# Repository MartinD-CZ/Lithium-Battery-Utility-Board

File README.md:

# Lithium Battery Utility Board

*see the article [here](http://embedblog.eu/?p=91)!*

versions (see the changelog for more information):
* V1.0 - proven, initial release
* V1.1 - minor tweaks, **not proven**
* V1.2 - major tweaks, proven

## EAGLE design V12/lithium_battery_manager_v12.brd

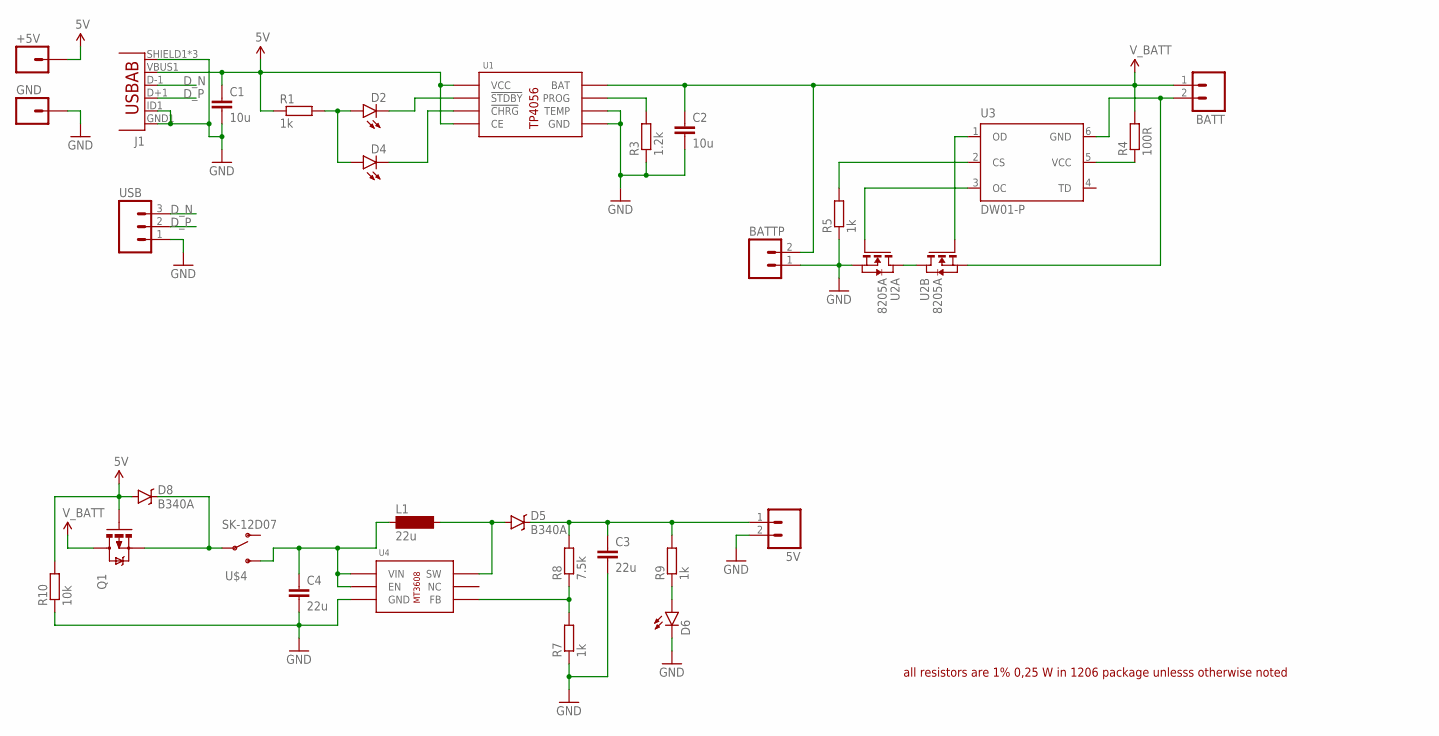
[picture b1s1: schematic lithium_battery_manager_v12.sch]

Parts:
5V: M02PTH3; 1X02_LONGPADS
+5V: M01OFFSET; 1X01_OFFSET
BATT: M02PTH3; 1X02_LONGPADS
BATTP: M02PTH3; 1X02_LONGPADS
C1, C2: 10u; C1206
C3, C4: 22u; C1206
D2, D4, D6: LED-CONN; LED5MM
D5, D8: B340A; SMA-DIODE
GND: M01OFFSET; 1X01_OFFSET
J1: USB-ABCONN-11794; USB-AB-MICRO-SMD_V03
L1: 22u; MS85
Q1: MOSFET-PCHANNEL; SOT23-3
R1, R5, R7, R9: 1k; R1206
R3: 1.2k; R1206
R4: 100R; R1206
R8: 7.5k; R1206
R10: 10k; R1206
U1: TP4056; SOP8
U2: 8205A; TSSOP8
U3: DW01-P; SOT23-6L
U4: MT3608; SOT23-6
U$4: SK-12D07; SK12SWITCH
USB: M03PTH; 1X03

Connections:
5V: +5V.1, C1.1, D8.A, J1.VBUS1 (VBUS), Q1.1 (G), R1.1, R10.2, U1.4 (VCC), U1.8 (CE)
D_N: J1.D-1 (D-), USB.3
D_P: J1.D+1 (D+), USB.2
GND: 5V.2, BATTP.1, C1.2, C2.2, C3.2, C4.2, D6.K (C), GND.1, J1.GND1 (GND), J1.ID1 (USBID), J1.SHIELD1 (SHIELD), J1.SHIELD2 (SHIELD), J1.SHIELD3 (SHIELD), R3.1, R5.1, R7.1, R10.1, U1.1 (TEMP), U1.3 (GND), U2.2 (S), U2.3 (S), U4.2 (GND), USB.1
unnamed: C4.1, L1.1, U4.4 (EN), U4.5 (VIN), U$4.IN (S)
unnamed: D2.K (C), U1.6 (!STDBY)
unnamed: D2.A, D4.A, R1.2
unnamed: R3.2, U1.2 (PROG)
unnamed: R4.1, U3.5 (VCC)
unnamed: D4.K (C), U1.7 (!CHRG)
unnamed: BATT.2, U2.6 (S), U2.7 (S), U3.6 (GND)
unnamed: U2.1 (D), U2.8 (D)
unnamed: U2.5 (G), U3.1 (OD)
unnamed: U2.4 (G), U3.3 (OC)
unnamed: D5.A, L1.2, U4.1 (SW)
unnamed: R5.2, U3.2 (CS)
unnamed: R7.2, R8.1, U4.3 (FB)
unnamed: D6.A, R9.1
unnamed: D8.C, Q1.2 (S), U$4.P2
unnamed: 5V.1, C3.1, D5.C, R8.2, R9.2
V_BATT: BATT.1, BATTP.2, C2.1, Q1.3 (D), R4.2, U1.5 (BAT)

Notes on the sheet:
all resistors are 1% 0,25 W in 1206 package unlesss otherwise noted

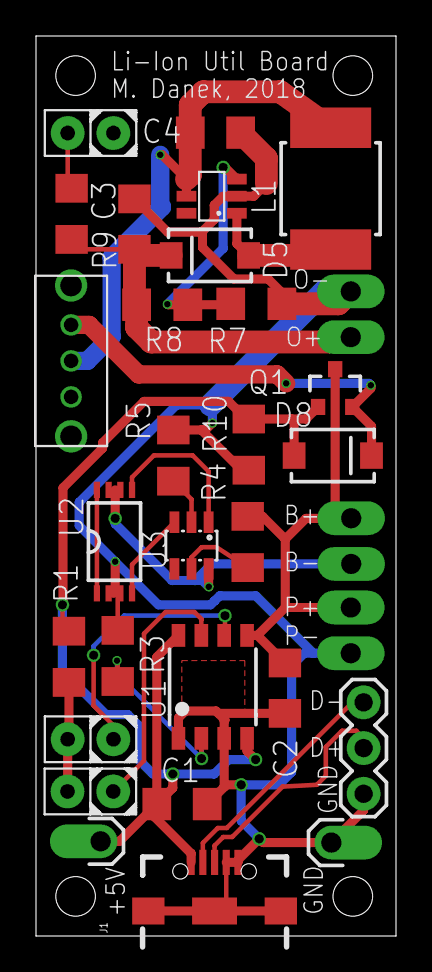
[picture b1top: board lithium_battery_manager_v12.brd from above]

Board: 2 copper layers, 20.0 x 50.0 mm, 31 parts (0 on the bottom side), 21 nets.

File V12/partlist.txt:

LITHIUM BATTERY MANAGER V1.2 PARTLIST
http://embedblog.eu/?p=91

Assembly variant: 

Part     Value           Device               Package                 Notes              

+5V                      M01OFFSET            1X01_OFFSET             just a pad, not a real part    
5V                       M02PTH3              1X02_LONGPADS           just a pad, not a real part        
BATT                     M02PTH3              1X02_LONGPADS           just a pad, not a real part     
BATTP                    M02PTH3              1X02_LONGPADS           just a pad, not a real part        
C1       10u             C-EUC1206            1206                
C2       10u             C-EUC1206            1206                
C3       22u             C-EUC1206            1206                
C4       22u             C-EUC1206            1206                
D2       LED-CONN        LED-CONN             LED5MM                  custom LED footprint, fits either 1206 SMD LED, 5 mm LED or wires              
D4       LED-CONN        LED-CONN             LED5MM                  custom LED footprint, fits either 1206 SMD LED, 5 mm LED or wires               
D5       B340A           DIODE-SCHOTTKY-B340A SMA-DIODE            
D6       LED-CONN        LED-CONN             LED5MM                  custom LED footprint, fits either 1206 SMD LED, 5 mm LED or wires               
D8       B340A           DIODE-SCHOTTKY-B340A SMA-DIODE            
GND                      M01OFFSET            1X01_OFFSET             just a pad, not a real part          
J1                       USB-ABCONN-11794     USB-AB-MICRO-SMD_V03    microUSB connector - the kind with two plastic legs protruding down  
L1       22u             MS85                 MS85                    22 uH inductor, rated at least 2 A                 
Q1       MOSFET-PCHANNEL MOSFET-PCHANNEL      SOT23-3                 generic one, I used AO3419              
R1       1k              R-EU_R1206           1206                
R3       1.2k            R-EU_R1206           1206                
R4       100R            R-EU_R1206           1206                
R5       1k              R-EU_R1206           1206                
R7       1k              R-EU_R1206           1206                
R8       7.5k            R-EU_R1206           1206                
R9       1k              R-EU_R1206           1206                
R10      10k             R-EU_R1206           1206                
U$4      SK-12D07        SK-12D07             SK12SWITCH           
U1       TP4056          TP4056               SOP8                 
U2       8205A           8205A                TSSOP8               
U3       DW01-P          DW01-P               SOT23-6L             
U4       MT3608          MT3608               SOT23-6              
USB                      M03PTH               1X03                    just a pad, not a real part

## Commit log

2017-12-25 MD modified
2017-12-25 MD modifed again
2018-01-08 added load sharing explanation
2018-11-22 V1.2 initial

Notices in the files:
parts and their libraries:
SparkFun-Connectors: Licensing: Creative Commons ShareAlike 4.0 International - https://creativecommons.org/licenses/by-sa/4.0
